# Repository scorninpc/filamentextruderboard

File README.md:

# Filament Extruder Board

Board to control heater and step motor for PET filament extruder

## Media

https://imgur.com/a/M2m6THj

## Tips

- Use MOSFET module to connect hotend. If you use 25A MOSFET module, this work only with 12v, so wire here (https://imgur.com/slLvls0) to use 5v of arduino

## How to use

- ENTER button to change what configure. Indicated by arrow
- UP and DOWN configure the value of indicated device
- LONG PRESS ENTER to start or stop the device indicated by arrow

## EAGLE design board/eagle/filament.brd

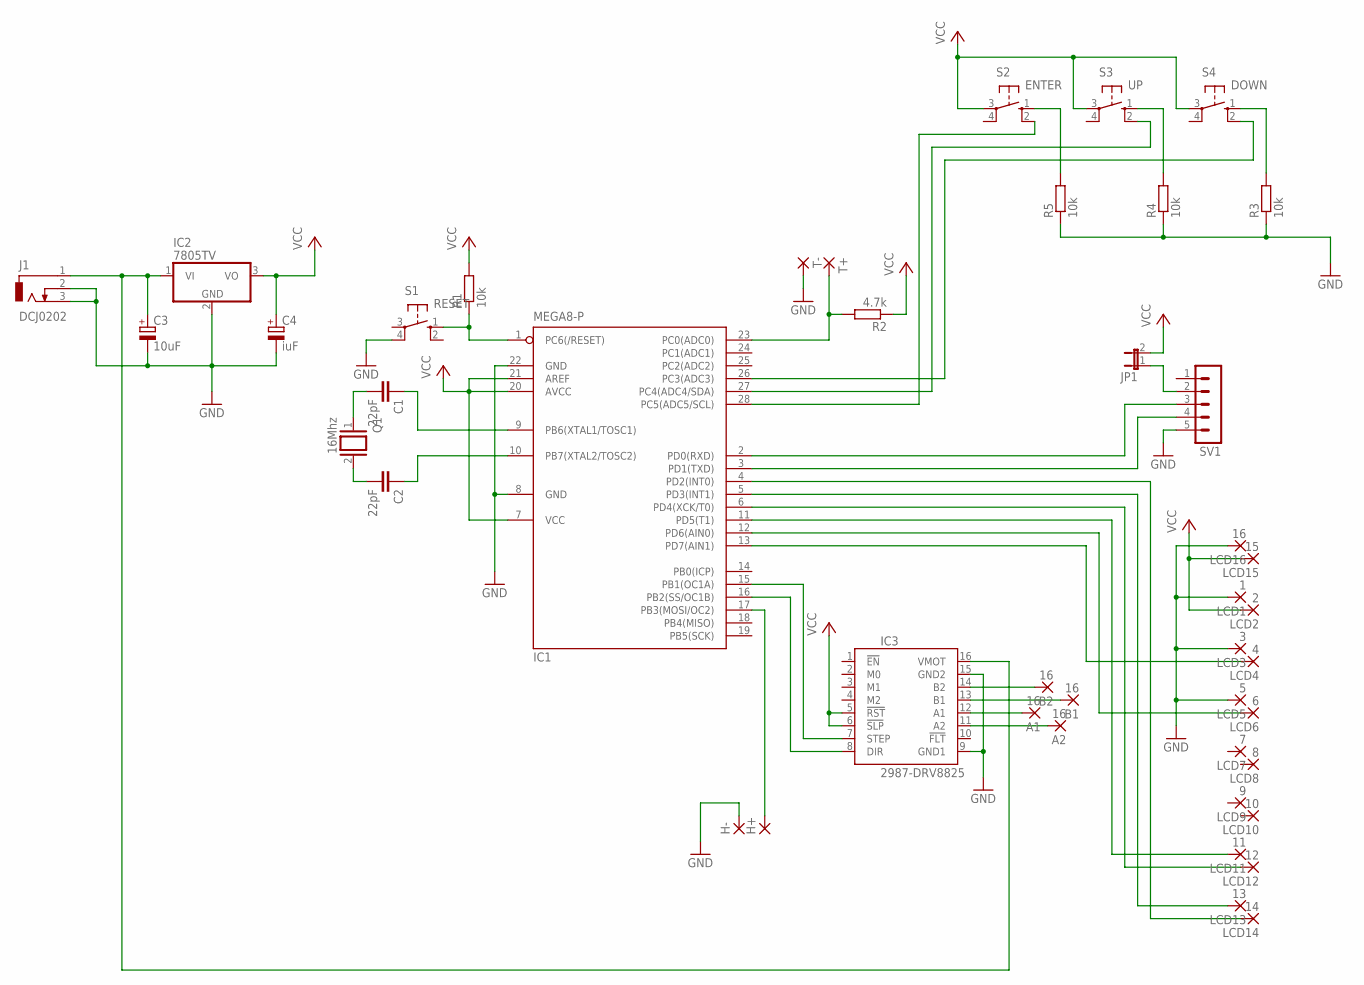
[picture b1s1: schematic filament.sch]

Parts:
A1, A2: 16; 1,6/0,8
B1, B2: 16; 1,6/0,8
C1, C2: 22pF; C050-025X075
C3: 10uF; E2-5
C4: iuF; E2-5
H+: 1,6/0,8
H-: 1,6/0,8
IC1: MEGA8-P; DIL28-3
IC2: 7805TV; TO220V
IC3: 2987-DRV8825; DRV8825
J1: DCJ0202
JP1: JP1E; JP1
LCD1: 1; 1,6/0,8
LCD2: 2; 1,6/0,8
LCD3: 3; 1,6/0,8
LCD4: 4; 1,6/0,8
LCD5: 5; 1,6/0,8
LCD6: 6; 1,6/0,8
LCD7: 7; 1,6/0,8
LCD8: 8; 1,6/0,8
LCD9: 9; 1,6/0,8
LCD10: 10; 1,6/0,8
LCD11: 11; 1,6/0,8
LCD12: 12; 1,6/0,8
LCD13: 13; 1,6/0,8
LCD14: 14; 1,6/0,8
LCD15: 15; 1,6/0,8
LCD16: 16; 1,6/0,8
Q1: 16Mhz; QS
R1, R3, R4, R5: 10k; 0207/10
R2: 4.7k; 0207/10
S1: RESET; B3F-10XX
S2: ENTER; B3F-10XX
S3: UP; B3F-10XX
S4: DOWN; B3F-10XX
SV1: MA05-1
T+: 1,6/0,8
T-: 1,6/0,8

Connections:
GND: C3.-, C4.-, H-.1, IC1.8 (GND), IC1.22 (GND), IC2.2 (GND), IC3.9 (GND1), IC3.15 (GND2), J1.2, J1.3, LCD1.1, LCD3.1, LCD5.1, LCD16.1, R3.1, R4.1, R5.1, S1.4 (P1), SV1.5, T-.1
unnamed: C1.2, Q1.1
unnamed: C2.2, Q1.2
unnamed: C2.1, IC1.10 (PB7(XTAL2/TOSC2))
unnamed: C1.1, IC1.9 (PB6(XTAL1/TOSC1))
unnamed: IC1.1 (PC6(/RESET)), R1.1, S1.1 (S)
unnamed: B2.1, IC3.14 (B2)
unnamed: IC1.3 (PD1(TXD)), SV1.4
unnamed: IC1.2 (PD0(RXD)), SV1.3
unnamed: JP1.1, SV1.2
unnamed: IC1.4 (PD2(INT0)), LCD14.1
unnamed: IC1.5 (PD3(INT1)), LCD13.1
unnamed: IC1.6 (PD4(XCK/T0)), LCD12.1
unnamed: IC1.11 (PD5(T1)), LCD11.1
unnamed: IC1.23 (PC0(ADC0)), R2.2, T+.1
unnamed: IC1.13 (PD7(AIN1)), LCD4.1
unnamed: H+.1, IC1.17 (PB3(MOSI/OC2))
unnamed: IC1.12 (PD6(AIN0)), LCD6.1
unnamed: R5.2, S2.1 (S)
unnamed: R4.2, S3.1 (S)
unnamed: R3.2, S4.1 (S)
unnamed: IC1.28 (PC5(ADC5/SCL)), S2.2 (S1)
unnamed: IC1.27 (PC4(ADC4/SDA)), S3.2 (S1)
unnamed: IC1.26 (PC3(ADC3)), S4.2 (S1)
unnamed: IC1.15 (PB1(OC1A)), IC3.7 (STEP)
unnamed: IC1.16 (PB2(SS/OC1B)), IC3.8 (DIR)
unnamed: B1.1, IC3.13 (B1)
unnamed: C3.+, IC2.1 (VI), IC3.16 (VMOT), J1.1
unnamed: A1.1, IC3.12 (A1)
unnamed: A2.1, IC3.11 (A2)
VCC: C4.+, IC1.7 (VCC), IC1.20 (AVCC), IC1.21 (AREF), IC2.3 (VO), IC3.5 (!RST), IC3.6 (!SLP), JP1.2, LCD2.1, LCD15.1, R1.2, R2.1, S2.3, S3.3, S4.3

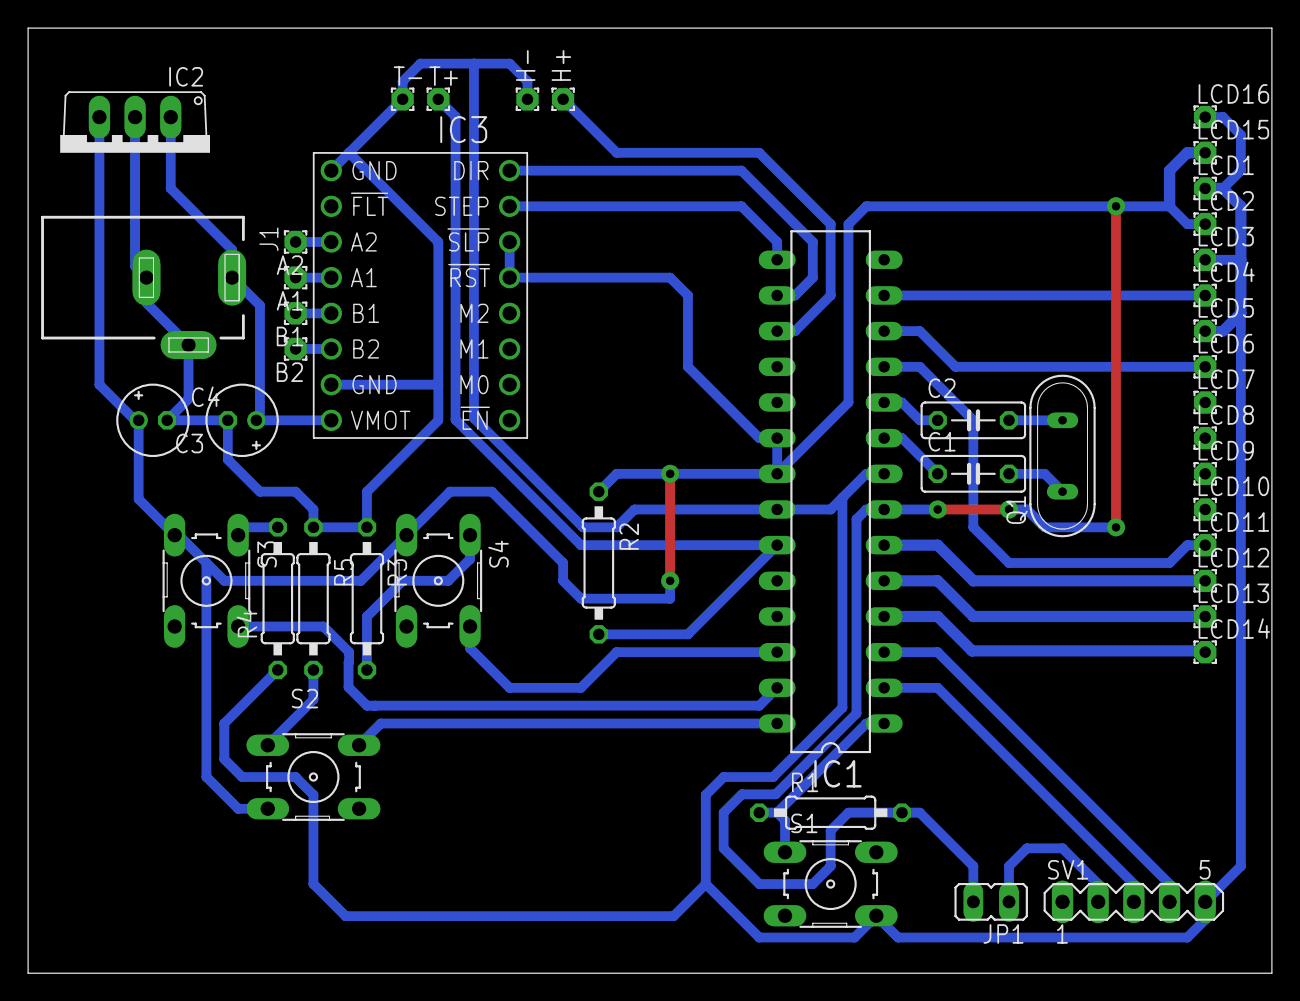
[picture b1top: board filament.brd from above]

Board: 2 copper layers, 88.6 x 67.3 mm, 44 parts (0 on the bottom side), 31 nets.

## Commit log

2021-10-15 Added long press of 3s on temp to on/off the heater Added * to show if heater is on or off Correction of target value if its less than 100
2021-10-15 added PID control to heater
2021-10-15 added long press to on/off motor and heater added icon to indicate if motor and heater is on or off added initial info of motor on screen added last config (motor speed and destiny temperature) to EE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
2021-10-15 fix start and stop motor
2021-10-24 Added heater to PWM pin Added step driver for 1/8 microsteps for less noise Removed lib to get temperature, so now we added a non-blocking read temperature for 3950 Added accelstepper for motor step 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
2021-10-24 Fixed unnecessary thermistor lib fix PID to run without heather enabled (need to rewrite this PID method, its not good for high temps)
2021-10-26 Removed the time for calc temperature. now the loop get the 5 lasts read, and calculate the temperature. PID must be real time
